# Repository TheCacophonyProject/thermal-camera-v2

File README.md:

# thermal-camera-v2

## Running tc2-panel.py (KiKit)

`tc2-panel.py` uses [KiKit](https://yaqwsx.github.io/KiKit/) to build the manufacturing panel from the individual board files.

```sh
# Create a venv that inherits the system site-packages (needed for pcbnew)
python3 -m venv --system-site-packages ~/.venvs/kikit
source ~/.venvs/kikit/bin/activate

# Install kikit and the other packages tc2-panel.py needs.
# pcbnewTransition is pinned >=0.5 because older versions assume a pre-KiCad-6
# pcbnew API (e.g. DRAWSEGMENT) and crash against current KiCad.
pip install kikit shapely "pcbnewTransition>=0.5"
```

Once the venv exists, running the panel script again only needs:

```sh
source ~/.venvs/kikit/bin/activate
cd /path/to/thermal-camera-v2
python3 tc2-panel.py
```

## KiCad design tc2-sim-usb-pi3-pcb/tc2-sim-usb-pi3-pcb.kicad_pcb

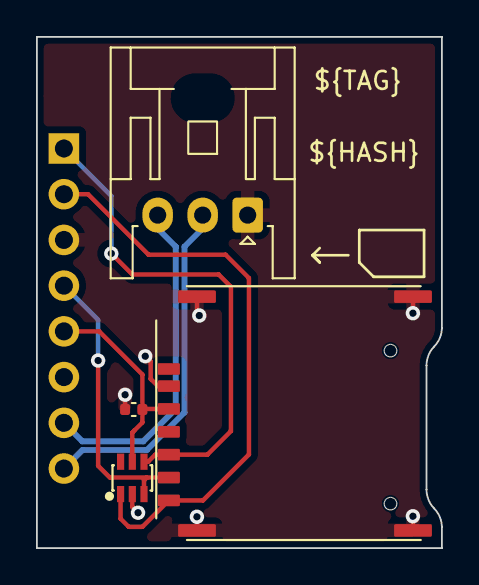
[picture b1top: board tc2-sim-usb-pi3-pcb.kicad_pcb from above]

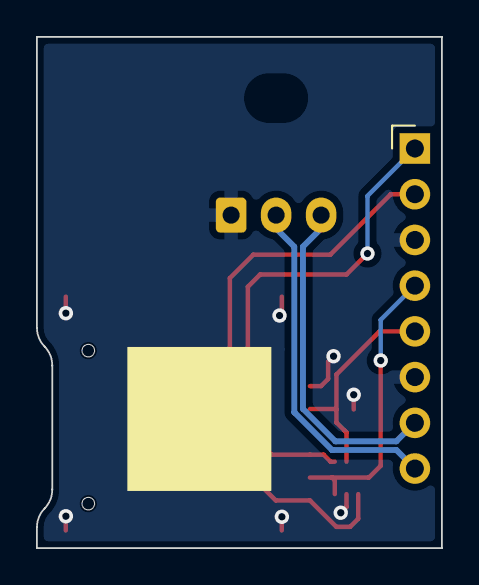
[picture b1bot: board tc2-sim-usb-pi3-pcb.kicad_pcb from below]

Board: 4 copper layers, 22.5 x 28.4 mm, 6 parts (2 on the bottom side), 7 nets.

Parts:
C1: 220nF; C_0402_1005Metric
D1: SMF05CT1G; SOT-363_L2.0-W1.3-P0.65-LS2.1-BR
J1: Conn_01x08; rpi3-usb-sim-PinHeader_1x08
J2: Conn_01x03; JST_XA_S03B-XASK-1_1x03_P2.50mm_Horizontal
U1: K-DYX-010
U2: JLCPCB_QR_8mm

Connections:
4G_USB_D+: J1.7, J2.3
4G_USB_D-: J1.8, J2.2
GND: C1.1, D1.2, J1.3, J1.6, J2.1, U1.C5 (Gnd), U1.MP, U1.MP_2 (MP), U1.MP_3 (MP), U1.MP_4 (MP)
USIM_CLK: D1.1, J1.2, U1.C3 (CLK)
USIM_DATA: D1.3, J1.4, U1.C7 (I/O)
USIM_RST: D1.4, J1.1, U1.C2 (RST)
USIM_VDD: C1.2, D1.5, J1.5, U1.C1 (Vcc)

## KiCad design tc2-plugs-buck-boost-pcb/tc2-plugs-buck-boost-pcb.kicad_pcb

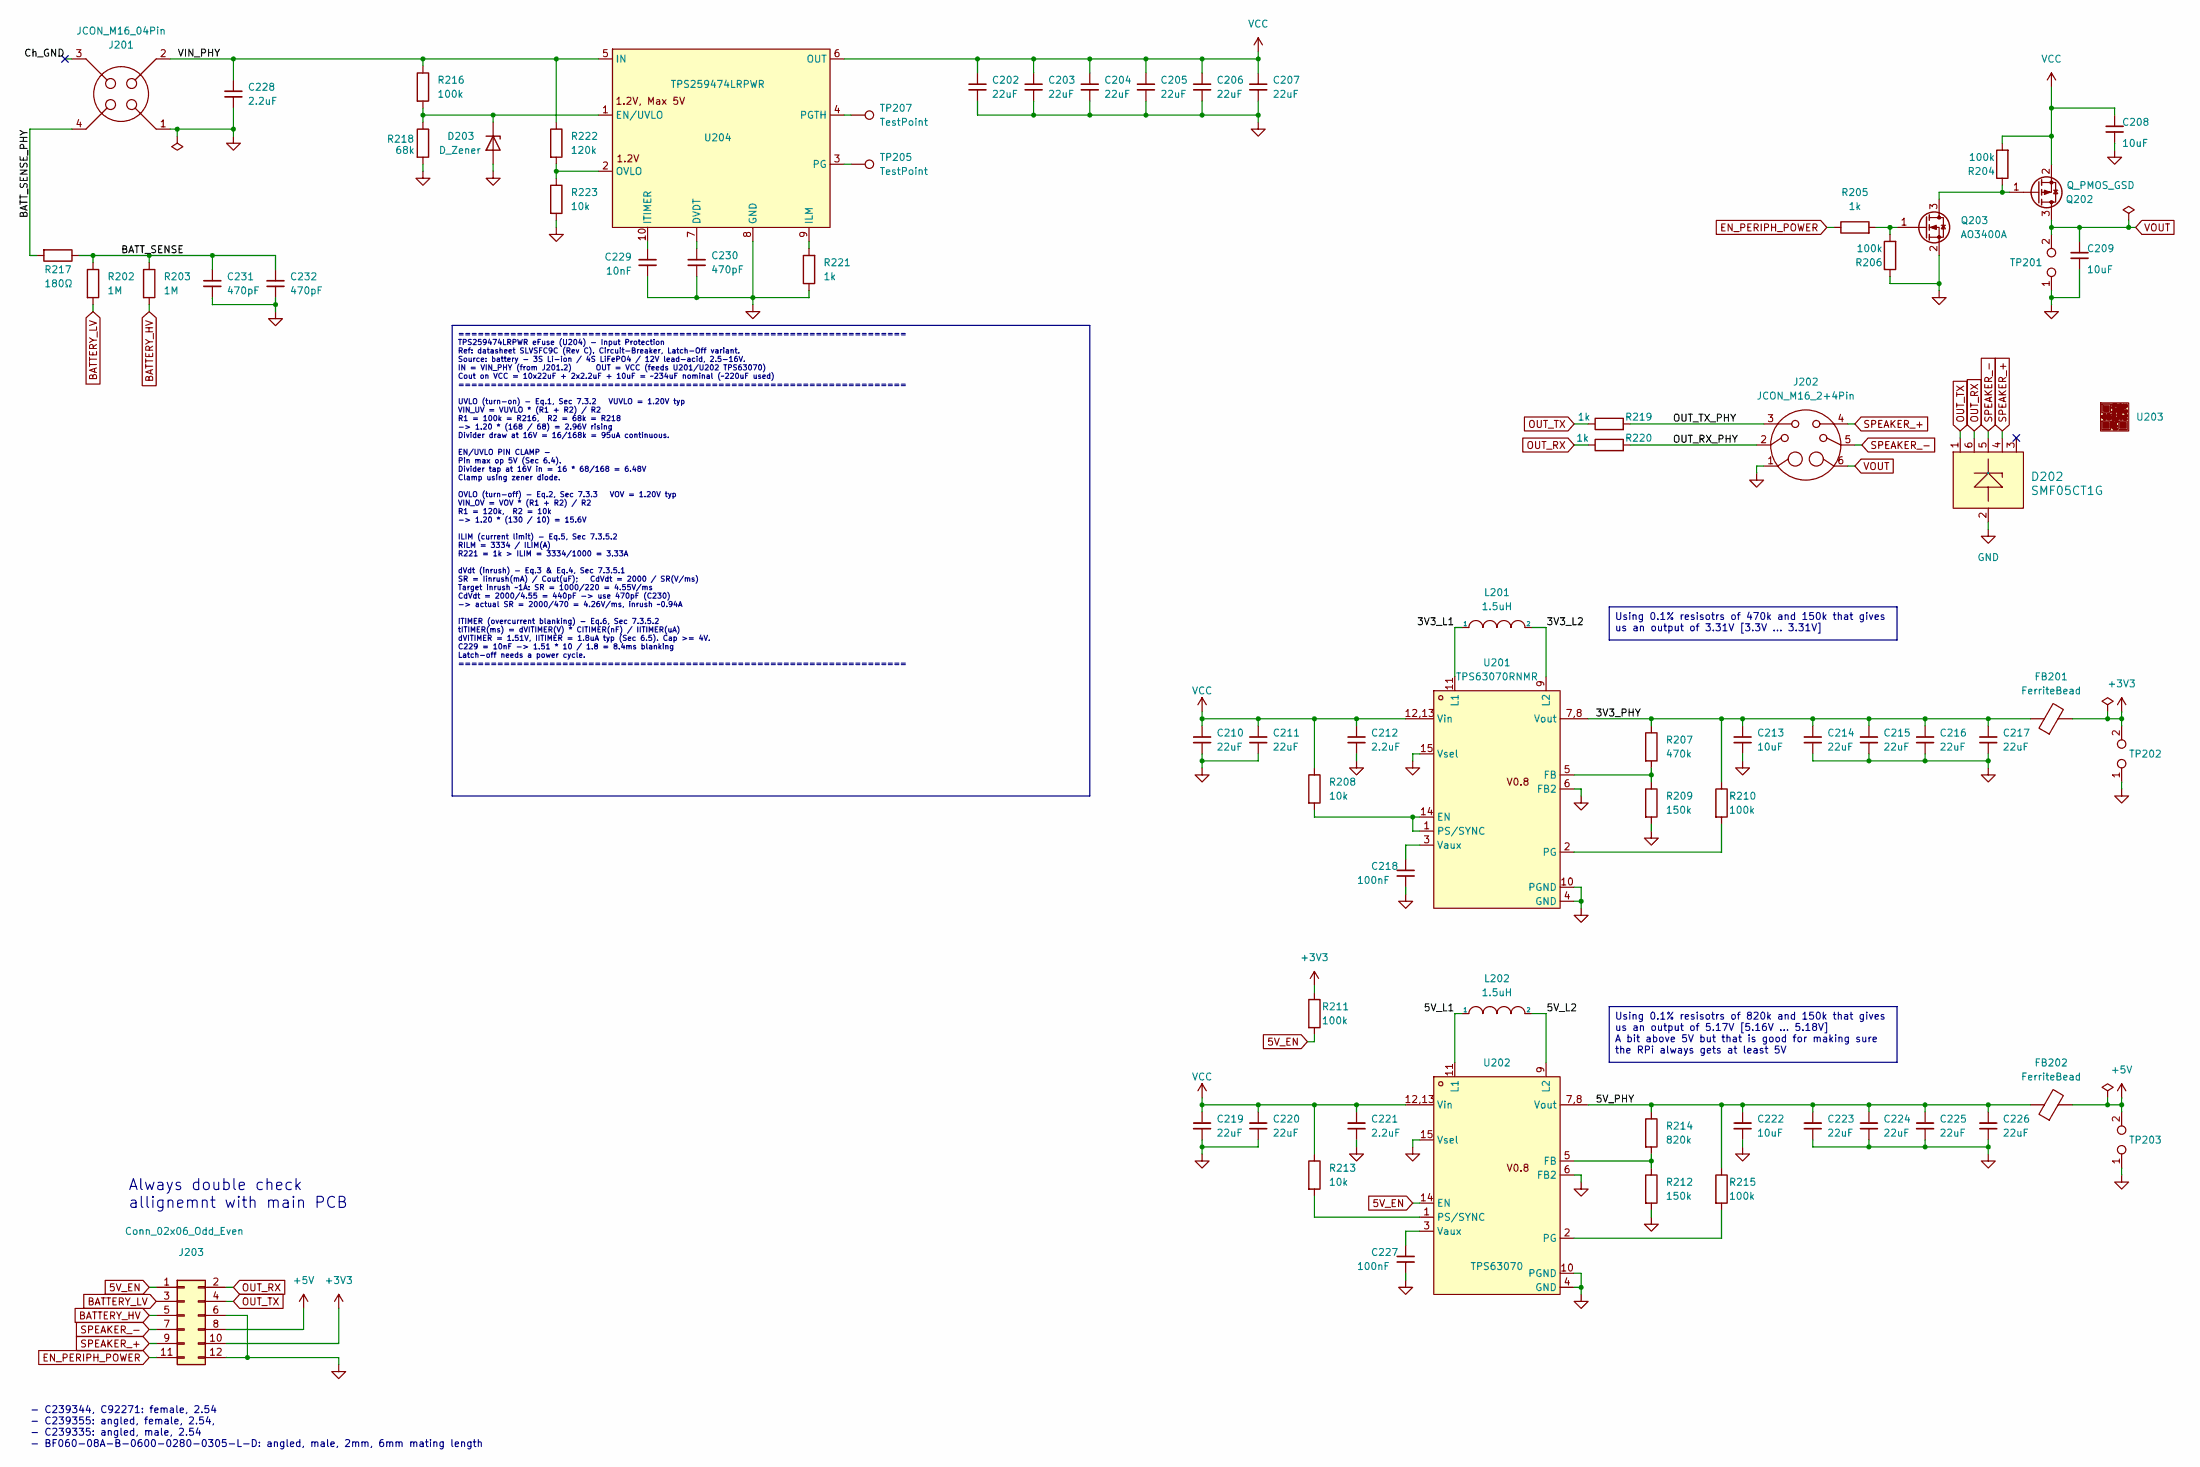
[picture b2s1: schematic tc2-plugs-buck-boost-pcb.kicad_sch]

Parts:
C202, C203, C204, C205, C206, C207, C210, C211, C219, C220: 22uF; C_0805_2012Metric; LCSC Part C45783
C208, C209: 10uF; C_0603_1608Metric; LCSC Part C19702
C212, C221, C228: 2.2uF; C_0402_1005Metric; LCSC Part C159814
C213, C222: 10uF; C_0402_1005Metric; LCSC Part C15525
C214, C215, C216, C217, C223, C224, C225, C226: 22uF; C_0603_1608Metric; LCSC Part C86295
C218, C227: 100nF; C_0402_1005Metric; LCSC Part C100072
C229: 10nF; C_0402_1005Metric; LCSC Part C15195
C230, C231, C232: 470pF; C_0402_1005Metric; LCSC Part C1537
D202: SMF05CT1G; SOT-363_L2.0-W1.3-P0.65-LS2.1-BR; LCSC Part C15879
D203: D_Zener; D_SOD-323; LCSC Part C136181
FB201, FB202: FerriteBead; L_0805_2012Metric; LCSC Part C76818
J201: JCON_M16_04Pin; jcon-4pin_m16
J202: JCON_M16_2+4Pin; jcon-2+4pin-m16
J203: Conn_02x06_Odd_Even; PinHeader_2x06_P2.00mm_Horizontal; Digikey 2073-BF060-12A-B-0600-0280-0305-L-D-ND
L201, L202: 1.5uH; L_1008_2520Metric; LCSC Part C5179452
Q202: Q_PMOS_GSD; SOT-23; LCSC Part C15127
Q203: AO3400A; SOT-23; LCSC Part C20917
R202, R203: 1M; R_0603_1608Metric; LCSC Part C326730
R204, R206, R210, R211, R215, R216: 100k; R_0402_1005Metric; LCSC Part C25741
R205, R219, R220, R221: 1k; R_0402_1005Metric; LCSC Part C11702
R207: 470k; R_0402_1005Metric; LCSC Part C319591
R208, R213, R223: 10k; R_0402_1005Metric; LCSC Part C25744
R209, R212: 150k; R_0402_1005Metric; LCSC Part C723770
R214: 820k; R_0402_1005Metric; LCSC Part C4042952
R217: 180Ω; R_0402_1005Metric; LCSC Part C38941
R218: 68k; R_0402_1005Metric; LCSC Part C445618
R222: 120k; R_0402_1005Metric; LCSC Part C25750
TP201, TP202, TP203: TestPoint_2Pole; test-point-2p
TP205, TP207: TestPoint; TP_PAD
U201: TPS63070RNMR; TPS63070; LCSC Part C109322
U202: TPS63070; LCSC Part C109322
U203: JLCPCB_QR_8mm
U204: TPS259474LRPWR; VQFN-10_L2.0-W2.0-P0.45-TL; LCSC Part C2864845

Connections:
5V_EN: J203.1, R211.2, U202.14 (EN)
+3V3: FB201.2, J203.10, R211.1, TP202.2
+5V: FB202.2, J203.8, TP203.2
/3V3_L1: L201.1, U201.11 (L1)
/3V3_L2: L201.2, U201.9 (L2)
/3V3_PHY: C213.1, C214.1, C215.1, C216.1, C217.1, FB201.1, R207.1, R210.1, U201.7,8 (Vout)
/5V_L1: L202.1, U202.11 (L1)
/5V_L2: L202.2, U202.9 (L2)
/5V_PHY: C222.1, C223.1, C224.1, C225.1, C226.1, FB202.1, R214.1, R215.1, U202.7,8 (Vout)
/BATT_SENSE: C231.1, C232.1, R202.1, R203.1, R217.1
/BATT_SENSE_PHY: J201.4, R217.2
/Ch_GND: J201.3
/OUT_RX_PHY: J202.2, R220.2
/OUT_TX_PHY: J202.3, R219.2
/VIN_PHY: C228.1, J201.2, R216.1, R222.1, U204.5 (IN)
BATTERY_HV: J203.5, R203.2
BATTERY_LV: J203.3, R202.2
EN_PERIPH_POWER: J203.11, R205.1
GND: C202.2, C203.2, C204.2, C205.2, C206.2, C207.2, C208.2, C209.2, C210.2, C211.2, C212.2, C213.2, C214.2, C215.2, C216.2, C217.2, C218.2, C219.2, C220.2, C221.2, C222.2, C223.2, C224.2, C225.2, C226.2, C227.2, C228.2, C229.2, C230.2, C231.2, C232.2, D202.2, D203.2 (A), J201.1, J202.1, J203.6, J203.12, Q203.2 (S), R206.1, R209.2, R212.2, R218.2, R221.1, R223.2, TP201.1, TP202.1, TP203.1, U201.4 (GND), U201.6 (FB2), U201.10 (PGND), U201.15 (Vsel), U202.4 (GND), U202.6 (FB2), U202.10 (PGND), U202.15 (Vsel), U204.8 (GND)
unnamed: D203.1 (K), R216.2, R218.1, U204.1 (EN/UVLO)
unnamed: Q202.1 (G), Q203.3 (D), R204.1
unnamed: Q203.1 (G), R205.2, R206.2
unnamed: R208.2, U201.1 (PS/SYNC), U201.14 (EN)
unnamed: R207.2, R209.1, U201.5 (FB)
unnamed: R210.2, U201.2 (PG)
unnamed: C218.1, U201.3 (Vaux)
unnamed: R212.1, R214.2, U202.5 (FB)
unnamed: R215.2, U202.2 (PG)
unnamed: R213.2, U202.1 (PS/SYNC)
unnamed: C227.1, U202.3 (Vaux)
unnamed: C230.1, U204.7 (DVDT)
unnamed: R221.2, U204.9 (ILM)
unnamed: C229.1, U204.10 (ITIMER)
unnamed: R222.2, R223.1, U204.2 (OVLO)
unnamed: TP205.1 (1_1), U204.3 (PG)
unnamed: TP207.1 (1_1), U204.4 (PGTH)
OUT_RX: D202.6, J203.2, R220.1
OUT_TX: D202.1, J203.4, R219.1
SPEAKER_+: D202.4, J202.4, J203.9
SPEAKER_-: D202.5, J202.5, J203.7
VCC: C202.1, C203.1, C204.1, C205.1, C206.1, C207.1, C208.1, C210.1, C211.1, C212.1, C219.1, C220.1, C221.1, Q202.2 (S), R204.2, R208.1, R213.1, U201.12,13 (Vin), U202.12,13 (Vin), U204.6 (OUT)
VOUT: C209.1, J202.6, Q202.3 (D), TP201.2

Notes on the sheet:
Always double check allignemnt with main PCB
- C239344, C92271: female, 2.54 - C239355: angled, female, 2.54, - C239335: angled, male, 2.54 - BF060-08A-B-0600-0280-0305-L-D: angled, male, 2mm, 6mm mating length
===================================================================== TPS259474LRPWR eFuse (U204) - Input Protection Ref: datasheet SLVSFC9C (Rev C). Circuit-Breaker, Latch-Off variant. Source: battery - 3S Li-ion / 4S LiFePO4 / 12V lead-acid, 2.5-16V. IN = VIN_PHY (from J201.2) OUT = VCC (feeds U2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
Using 0.1% resisotrs of 470k and 150k that gives us an output of 3.31V [3.3V ... 3.31V]
Using 0.1% resisotrs of 820k and 150k that gives us an output of 5.17V [5.16V ... 5.18V] A bit above 5V but that is good for making sure the RPi always gets at least 5V

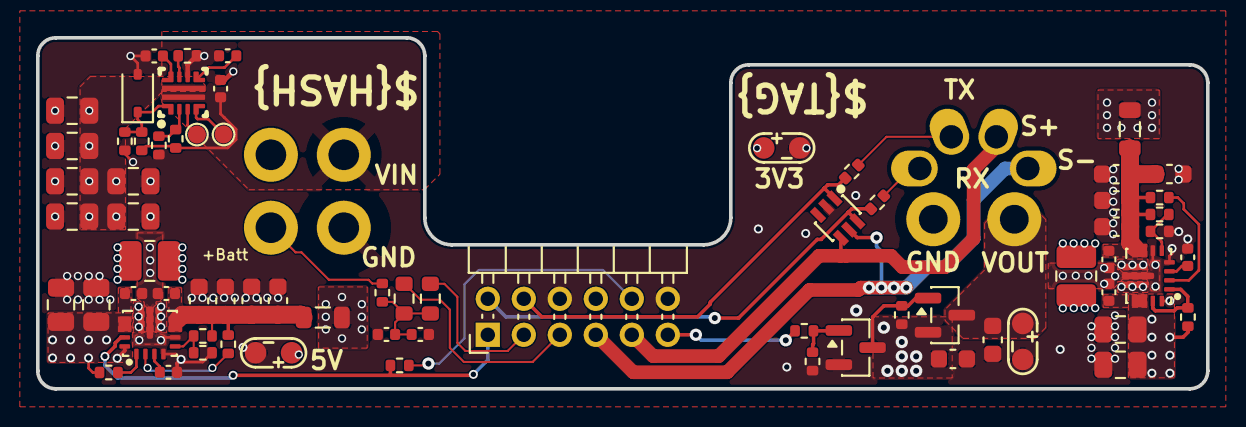
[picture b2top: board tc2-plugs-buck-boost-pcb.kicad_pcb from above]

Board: 6 copper layers, 65.0 x 19.5 mm, 73 parts (1 on the bottom side), 41 nets.

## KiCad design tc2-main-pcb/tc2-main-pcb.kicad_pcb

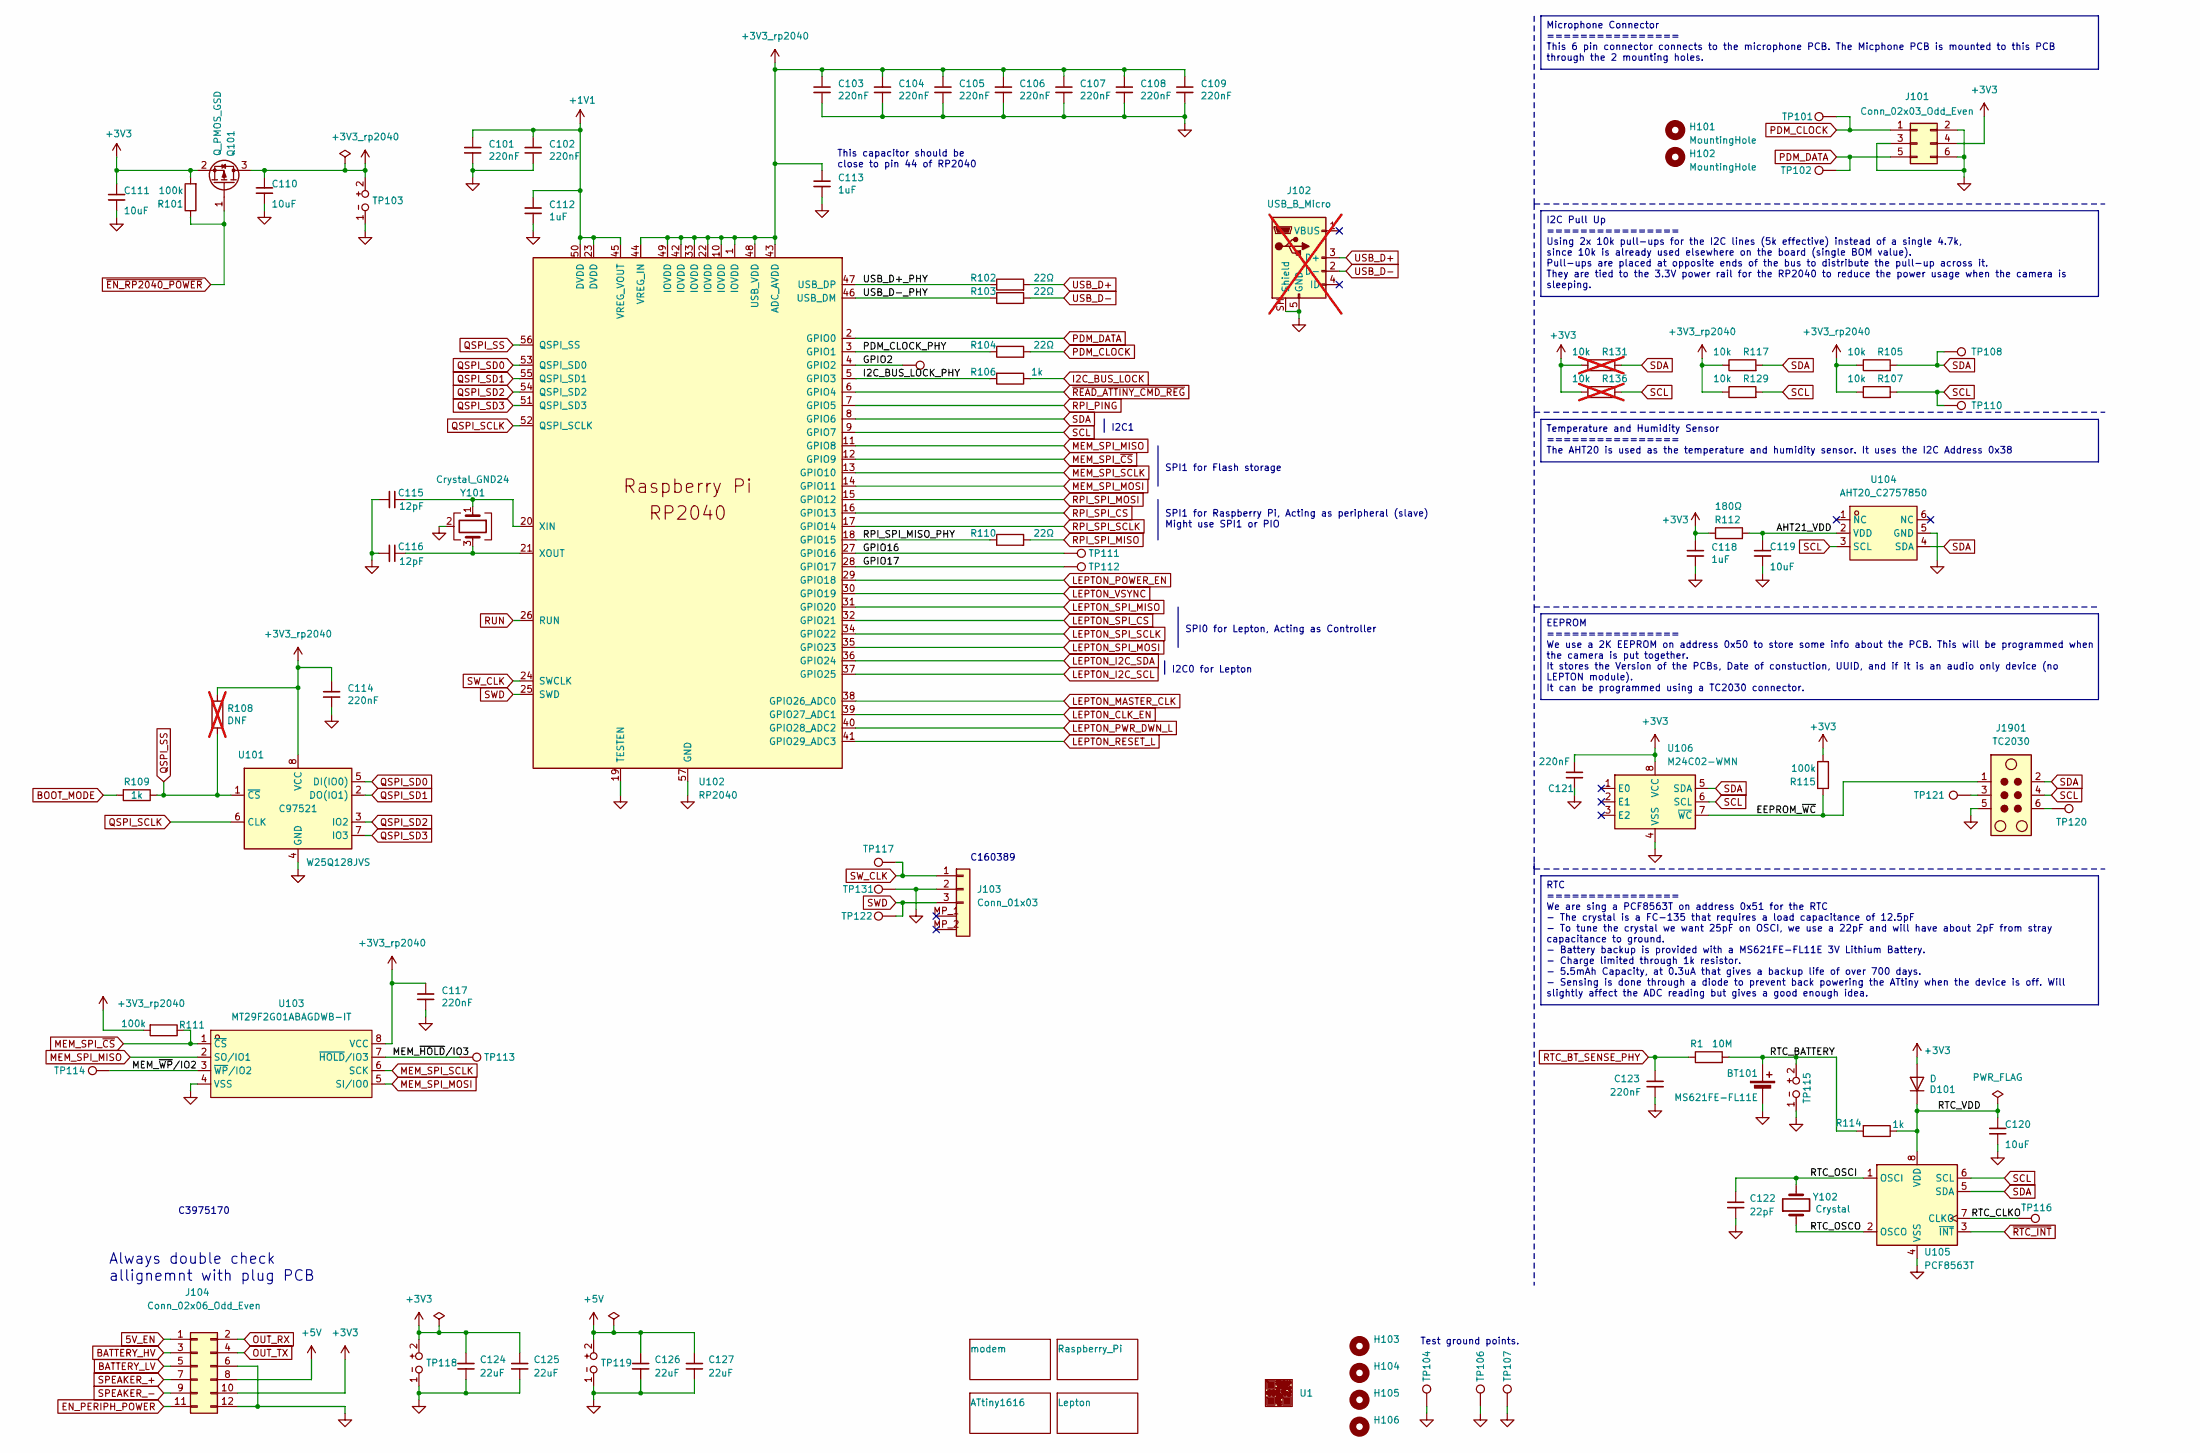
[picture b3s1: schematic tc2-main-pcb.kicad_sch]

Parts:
BT101: MS621FE-FL11E; CAP-SMD_FL11E; LCSC Part C80909
C101, C102, C103, C104, C105, C106, C107, C108, C109, C114, C117, C121, C123: 220nF; C_0402_1005Metric; LCSC Part C16772
C110, C111, C119, C120: 10uF; C_0603_1608Metric; LCSC Part C19702
C112, C113, C118: 1uF; C_0402_1005Metric; LCSC Part C52923
C115, C116: 12pF; C_0402_1005Metric; LCSC Part C1547
C122: 22pF; C_0402_1005Metric; LCSC Part C1555
C124, C125, C126, C127: 22uF; C_0603_1608Metric; LCSC Part C86295
D101: D; D_SOD-523; LCSC Part C668989
H101, H102: MountingHole; MountingHole_2.2mm_M2
H103, H104, H105, H106: MountingHole; MountingHole_3.2mm_M3
J101: Conn_02x03_Odd_Even; mic-pcb; LCSC Part C3975129
J102: USB_B_Micro; MICRO-USB-TH_MICRO-USB-A14; LCSC Part C145795; not fitted
J103: Conn_01x03; JST_SH_BM03B-SRSS-TB_1x03-1MP_P1.00mm_Vertical; LCSC Part C160389
J104: Conn_02x06_Odd_Even; power-pcb-3.1; Digikey BF100-12-A-D-1-0640-L-C
J1901: TC2030; Tag-Connect_TC2030-IDC-NL_2x03_P1.27mm_Vertical
Q101: Q_PMOS_GSD; SOT-23; LCSC Part C15127
R1: 10M; R_0402_1005Metric; LCSC Part C274900
R101, R111, R115: 100k; R_0402_1005Metric; LCSC Part C25741
R102, R103, R104, R110: 22Ω; R_0402_1005Metric; LCSC Part C25092
R105, R107, R117, R129: 10k; R_0402_1005Metric; LCSC Part C25744
R106, R109, R114: 1k; R_0402_1005Metric; LCSC Part C11702
R108: DNF; R_0402_1005Metric; not fitted
R112: 180Ω; R_0402_1005Metric; LCSC Part C38941
R131, R136: 10k; R_0402_1005Metric; LCSC Part C25744; not fitted
TP101, TP102, TP108, TP110, TP117, TP120, TP121, TP122, TP131: TestPoint; TestPoint_Pad_D1.0mm
TP103, TP115, TP118, TP119: TP_2P; test-point-2p
TP104, TP106, TP107: TestPoint; TestPoint_Loop_D2.54mm_Drill1.5mm_Beaded
TP109, TP111, TP112, TP113, TP114, TP116: TestPoint; TP
U1: JLCPCB_QR_8mm
U101: W25Q128JVS; SOIC-8_5.3x5.3mm_P1.27mm; LCSC Part C97521
U102: RP2040; RP2040-QFN-56; LCSC Part C2040
U103: MT29F2G01ABAGDWB-IT; U-PDFN-8_L6.0-W8.0-P1.27-BL; JLC Part Extended Part
U104: AHT20_C2757850; SENSOR-SMD_L3.0-W3.0-P1.00-BR; LCSC Part C2757850
U105: PCF8563T; SOIC-8_3.9x4.9mm_P1.27mm; LCSC Part C7440
U106: M24C02-WMN; SOIC-8_3.9x4.9mm_P1.27mm; LCSC Part C7562
Y101: Crystal_GND24; Crystal_SMD_3225-4Pin_3.2x2.5mm; LCSC Part C9002
Y102: Crystal; Crystal_SMD_3215-2Pin_3.2x1.5mm; LCSC Part C32346

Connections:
5V_EN: J104.1; also elsewhere on the board
+1V1: C101.1, C102.1, C112.1, U102.23 (DVDD), U102.45 (VREG_VOUT), U102.50 (DVDD)
+3V3: C111.1, C118.1, C121.2, C124.1, C125.1, D101.2 (A), J101.4, J104.10, Q101.2 (S), R101.2, R112.1, R115.2, R131.1, R136.1, TP118.2, U106.8 (VCC); also elsewhere on the board
+3V3_rp2040: C103.1, C104.1, C105.1, C106.1, C107.1, C108.1, C109.1, C110.1, C113.1, C114.1, C117.1, Q101.3 (D), R105.1, R107.1, R108.1, R111.2, R117.1, R129.1, TP103.2, U101.8 (VCC), U102.1 (IOVDD), U102.10 (IOVDD), U102.22 (IOVDD), U102.33 (IOVDD), U102.42 (IOVDD), U102.43 (ADC_AVDD), U102.44 (VREG_IN), U102.48 (USB_VDD), U102.49 (IOVDD), U103.8 (VCC)
+5V: C126.1, C127.1, J104.8, TP119.2; also elsewhere on the board
/AHT21_VDD: C119.1, R112.2, U104.2 (VDD)
/EEPROM_~WC: J1901.1, R115.1, U106.7 (~WC)
/GPIO2: TP109.1 (1_1), U102.4 (GPIO2)
/GPIO16: TP111.1 (1_1), U102.27 (GPIO16)
/GPIO17: TP112.1 (1_1), U102.28 (GPIO17)
/I2C_BUS_LOCK_PHY: R106.2, U102.5 (GPIO3)
/MEM_~HOLD/IO3: TP113.1 (1_1), U103.7 (~HOLD/IO3)
/MEM_~WP/IO2: TP114.1 (1_1), U103.3 (~WP/IO2)
/PDM_CLOCK_PHY: R104.1, U102.3 (GPIO1)
/RPI_SPI_MISO_PHY: R110.1, U102.18 (GPIO15)
/RTC_BATTERY: BT101.1 (+), R1.2, R114.2, TP115.2
/RTC_CLKO: TP116.1 (1_1), U105.7 (CLKO)
/RTC_OSCI: C122.1, U105.1 (OSCI), Y102.2
/RTC_OSCO: U105.2 (OSCO), Y102.1
/RTC_VDD: C120.1, D101.1 (K), R114.1, U105.8 (VDD)
/USB_D+_PHY: R102.1, U102.47 (USB_DP)
/USB_D-_PHY: R103.1, U102.46 (USB_DM)
BATTERY_HV: J104.3; also elsewhere on the board
BATTERY_LV: J104.5; also elsewhere on the board
BOOT_MODE: R109.2; also elsewhere on the board
EN_PERIPH_POWER: J104.11; also elsewhere on the board
GND: BT101.2 (-), C101.2, C102.2, C103.2, C104.2, C105.2, C106.2, C107.2, C108.2, C109.2, C110.2, C111.2, C112.2, C113.2, C114.2, C115.1, C116.1, C117.2, C118.2, C119.2, C120.2, C121.1, C122.2, C123.2, C124.2, C125.2, C126.2, C127.2, J101.2, J101.3, J101.6, J102.5 (GND), J102.SH (Shield), J103.2, J104.6, J104.12, J1901.5, TP103.1, TP104.1 (1_1), TP106.1 (1_1), TP107.1 (1_1), TP115.1, TP118.1, TP119.1, TP131.1 (1_1), U101.4 (GND), U102.19 (TESTEN), U102.57 (GND), U103.4 (VSS), U104.5 (GND), U105.4 (VSS), U106.4 (VSS), Y101.2 (G), Y101.4 (G); also elsewhere on the board
I2C_BUS_LOCK: R106.1; also elsewhere on the board
LEPTON_CLK_EN: U102.39 (GPIO27_ADC1); also elsewhere on the board
LEPTON_I2C_SCL: U102.37 (GPIO25); also elsewhere on the board
LEPTON_I2C_SDA: U102.36 (GPIO24); also elsewhere on the board
LEPTON_MASTER_CLK: U102.38 (GPIO26_ADC0); also elsewhere on the board
LEPTON_POWER_EN: U102.29 (GPIO18); also elsewhere on the board
LEPTON_PWR_DWN_L: U102.40 (GPIO28_ADC2); also elsewhere on the board
LEPTON_RESET_L: U102.41 (GPIO29_ADC3); also elsewhere on the board
LEPTON_SPI_CS: U102.32 (GPIO21); also elsewhere on the board
LEPTON_SPI_MISO: U102.31 (GPIO20); also elsewhere on the board
LEPTON_SPI_MOSI: U102.35 (GPIO23); also elsewhere on the board
LEPTON_SPI_SCLK: U102.34 (GPIO22); also elsewhere on the board
LEPTON_VSYNC: U102.30 (GPIO19); also elsewhere on the board
MEM_SPI_MISO: U102.11 (GPIO8), U103.2 (SO/IO1)
MEM_SPI_MOSI: U102.14 (GPIO11), U103.5 (SI/IO0)
MEM_SPI_SCLK: U102.13 (GPIO10), U103.6 (SCK)
MEM_SPI_~CS: R111.1, U102.12 (GPIO9), U103.1 (~CS)
unnamed: J1901.3, TP121.1 (1_1)
unnamed: J1901.6, TP120.1 (1_1)
unnamed: C115.2, U102.20 (XIN), Y101.1
unnamed: C116.2, U102.21 (XOUT), Y101.3
OUT_RX: J104.2; also elsewhere on the board
OUT_TX: J104.4; also elsewhere on the board
PDM_CLOCK: J101.1, R104.2, TP101.1 (1_1)
PDM_DATA: J101.5, TP102.1 (1_1), U102.2 (GPIO0)
QSPI_SCLK: U101.6 (CLK), U102.52 (QSPI_SCLK)
QSPI_SD0: U101.5 (DI(IO0)), U102.53 (QSPI_SD0)
QSPI_SD1: U101.2 (DO(IO1)), U102.55 (QSPI_SD1)
QSPI_SD2: U101.3 (IO2), U102.54 (QSPI_SD2)
QSPI_SD3: U101.7 (IO3), U102.51 (QSPI_SD3)
QSPI_SS: R108.2, R109.1, U101.1 (~CS), U102.56 (QSPI_SS)
RPI_PING: U102.7 (GPIO5); also elsewhere on the board
RPI_SPI_CS: U102.16 (GPIO13); also elsewhere on the board
RPI_SPI_MISO: R110.2; also elsewhere on the board
RPI_SPI_MOSI: U102.15 (GPIO12); also elsewhere on the board
RPI_SPI_SCLK: U102.17 (GPIO14); also elsewhere on the board
RTC_BT_SENSE_PHY: C123.1, R1.1; also elsewhere on the board
RUN: U102.26 (RUN); also elsewhere on the board
SCL: J1901.4, R107.2, R129.2, R136.2, TP110.1 (1_1), U102.9 (GPIO7), U104.3 (SCL), U105.6 (SCL), U106.6 (SCL); also elsewhere on the board
SDA: J1901.2, R105.2, R117.2, R131.2, TP108.1 (1_1), U102.8 (GPIO6), U104.4 (SDA), U105.5 (SDA), U106.5 (SDA); also elsewhere on the board
SPEAKER_+: J104.7; also elsewhere on the board
SPEAKER_-: J104.9; also elsewhere on the board
SWD: J103.3, TP122.1 (1_1), U102.25 (SWD); also elsewhere on the board
SW_CLK: J103.1, TP117.1 (1_1), U102.24 (SWCLK); also elsewhere on the board
USB_D+: J102.3 (D+), R102.2
USB_D-: J102.2 (D-), R103.2
~EN_RP2040_POWER: Q101.1 (G), R101.1; also elsewhere on the board
~READ_ATTINY_CMD_REG: U102.6 (GPIO4); also elsewhere on the board
~RTC_INT: U105.3 (~INT); also elsewhere on the board

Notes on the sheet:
C160389
Test ground points.
SPI0 for Lepton, Acting as Controller
I2C1
C3975170
Always double check allignemnt with plug PCB
I2C0 for Lepton
This capacitor should be close to pin 44 of RP2040
SPI1 for Raspberry Pi, Acting as peripheral (slave) Might use SPI1 or PIO
SPI1 for Flash storage
I2C Pull Up ================ Using 2x 10k pull-ups for the I2C lines (5k effective) instead of a single 4.7k, since 10k is already used elsewhere on the board (single BOM value). Pull-ups are placed at opposite ends of the bus to distribute the pull-up across it. They are tied to the 3.3V power rai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
RTC ================ We are sing a PCF8563T on address 0x51 for the RTC - The crystal is a FC-135 that requires a load capacitance of 12.5pF - To tune the crystal we want 25pF on OSCI, we use a 22pF and will have about 2pF from stray capacitance to ground. - Battery backup is provided with a MS621F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
Temperature and Humidity Sensor ================ The AHT20 is used as the temperature and humidity sensor. It uses the I2C Address 0x38
Microphone Connector ================ This 6 pin connector connects to the microphone PCB. The Micphone PCB is mounted to this PCB through the 2 mounting holes.
EEPROM ================ We use a 2K EEPROM on address 0x50 to store some info about the PCB. This will be programmed when the camera is put together. It stores the Version of the PCBs, Date of constuction, UUID, and if it is an audio only device (no LEPTON module). It can be programmed using a TC20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

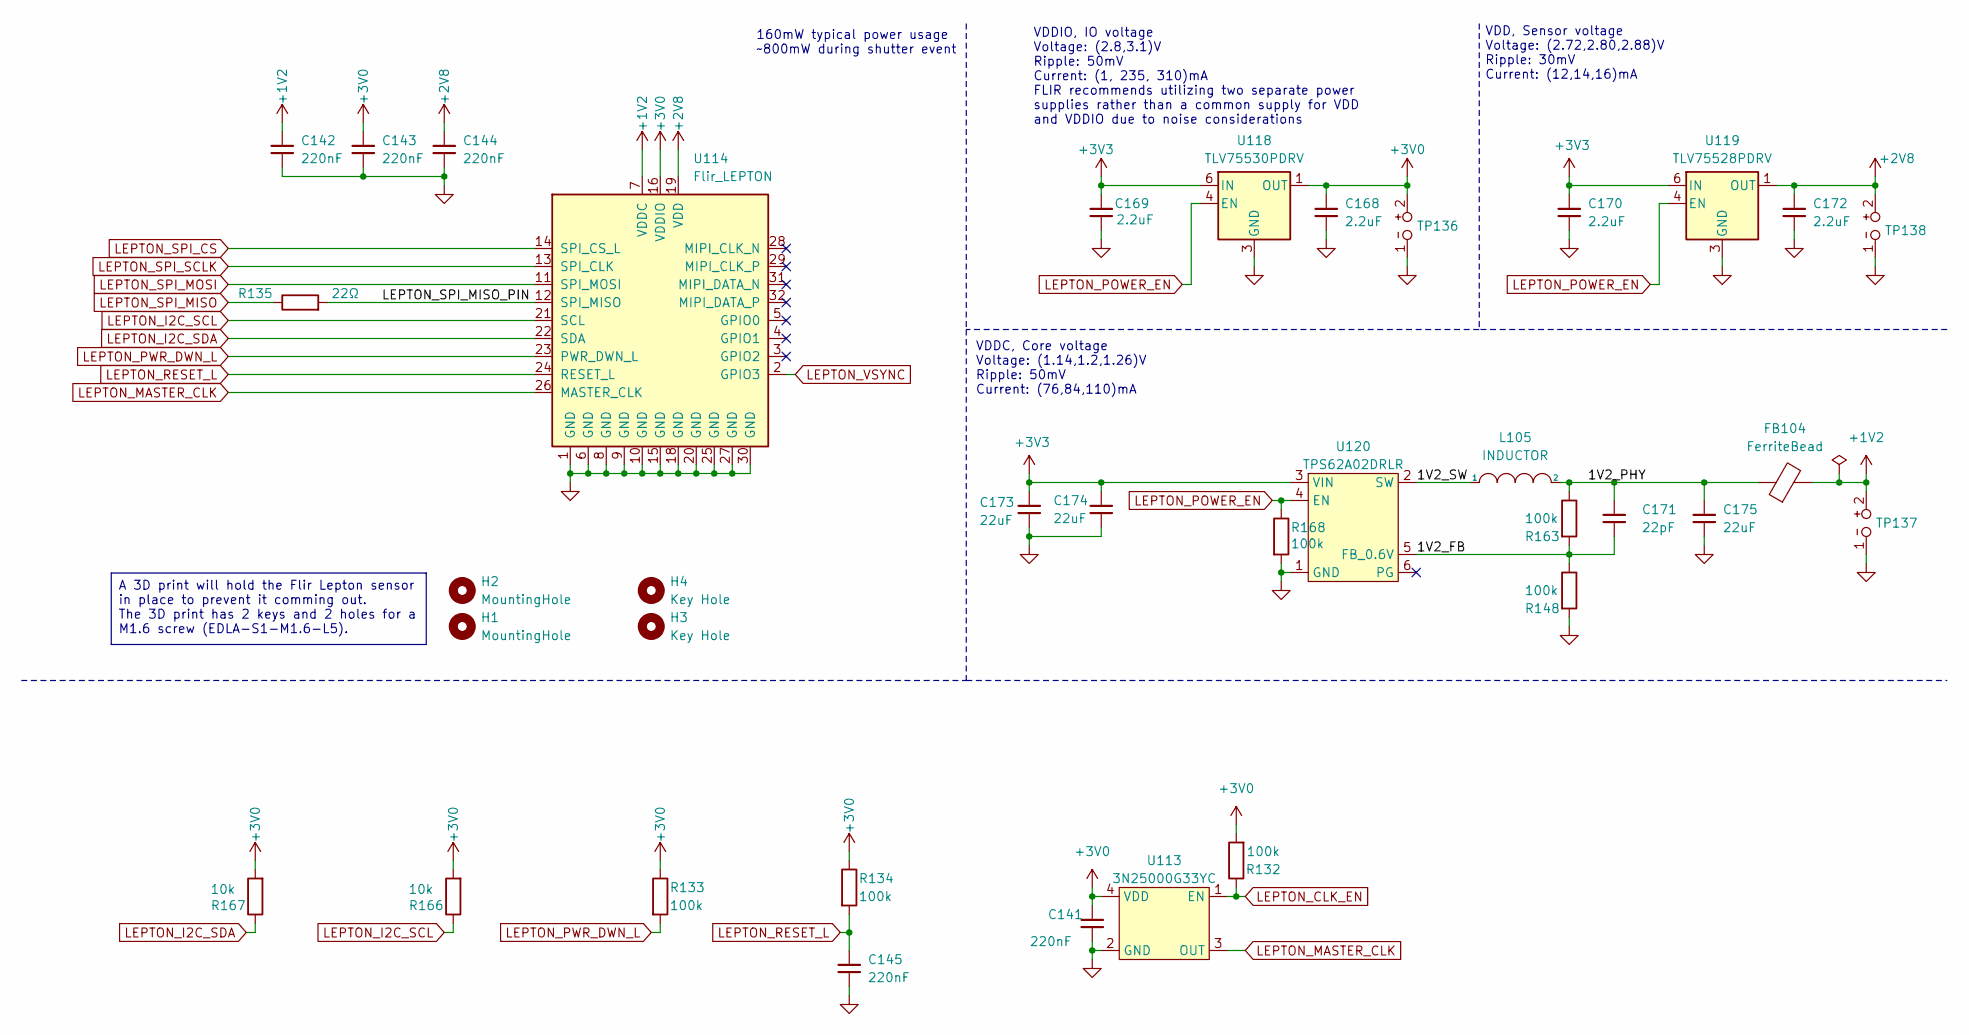
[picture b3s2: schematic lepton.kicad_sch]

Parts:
C141, C142, C143, C144, C145: 220nF; C_0402_1005Metric; LCSC Part C16772
C168, C169, C170, C172: 2.2uF; C_0402_1005Metric; LCSC Part C12530
C171: 22pF; C_0402_1005Metric; LCSC Part C1555
C173, C174, C175: 22uF; C_0603_1608Metric; LCSC Part C86295
FB104: FerriteBead; L_0805_2012Metric; LCSC Part C76818
H1, H2: MountingHole; MountingHole_1.8mm_M1.6
H3, H4: Key Hole; KeyHole_1.8mm
L105: INDUCTOR; L_1008_2520Metric; LCSC Part C285917
R132: 100k; R_0402_1005Metric; MPN RC1005F103CS; LCSC Part C25741
R133, R134, R148, R163, R168: 100k; R_0402_1005Metric; LCSC Part C25741
R135: 22Ω; R_0402_1005Metric; LCSC Part C25092
R166, R167: 10k; R_0402_1005Metric; LCSC Part C25744
TP136, TP137, TP138: TP_2P; test-point-2p
U113: 3N25000G33YC; Oscillator_SMD_Abracon_ASE-4Pin_3.2x2.5mm; JLCPCB C252341
U114: Flir_LEPTON; MOLEX_105028-1001; MPN 1050281001; LCSC Part C585422
U118: TLV75530PDRV; WSON-6-1EP_2x2mm_P0.65mm_EP1x1.6mm; LCSC Part C2859948
U119: TLV75528PDRV; WSON-6-1EP_2x2mm_P0.65mm_EP1x1.6mm; LCSC Part C2865214
U120: TPS62A02DRLR; SOT-563; LCSC Part C5350187

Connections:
+1V2: C142.1, FB104.2, TP137.2, U114.7 (VDDC)
+2V8: C144.1, C172.1, TP138.2, U114.19 (VDD), U119.1 (OUT)
+3V0: C141.1, C143.1, C168.1, R132.2, R133.1, R134.1, R166.2, R167.2, TP136.2, U113.4 (VDD), U114.16 (VDDIO), U118.1 (OUT)
+3V3: C169.1, C170.1, C173.1, C174.1, U118.6 (IN), U119.6 (IN), U120.3 (VIN); also elsewhere on the board
/Lepton/1V2_FB: C171.2, R148.1, R163.2, U120.5 (FB_0.6V)
/Lepton/1V2_PHY: C171.1, C175.1, FB104.1, L105.2, R163.1
/Lepton/1V2_SW: L105.1, U120.2 (SW)
/Lepton/LEPTON_SPI_MISO_PIN: R135.2, U114.12 (SPI_MISO)
GND: C141.2, C142.2, C143.2, C144.2, C145.2, C168.2, C169.2, C170.2, C172.2, C173.2, C174.2, C175.2, R148.2, R168.2, TP136.1, TP137.1, TP138.1, U113.2 (GND), U114.1 (GND), U114.6 (GND), U114.8 (GND), U114.9 (GND), U114.10 (GND), U114.15 (GND), U114.18 (GND), U114.20 (GND), U114.25 (GND), U114.27 (GND), U114.30 (GND), U118.3 (GND), U118.7 (GND), U119.3 (GND), U119.7 (GND), U120.1 (GND); also elsewhere on the board
LEPTON_CLK_EN: R132.1, U113.1 (EN); also elsewhere on the board
LEPTON_I2C_SCL: R166.1, U114.21 (SCL); also elsewhere on the board
LEPTON_I2C_SDA: R167.1, U114.22 (SDA); also elsewhere on the board
LEPTON_MASTER_CLK: U113.3 (OUT), U114.26 (MASTER_CLK); also elsewhere on the board
LEPTON_POWER_EN: R168.1, U118.4 (EN), U119.4 (EN), U120.4 (EN); also elsewhere on the board
LEPTON_PWR_DWN_L: R133.2, U114.23 (PWR_DWN_L); also elsewhere on the board
LEPTON_RESET_L: C145.1, R134.2, U114.24 (RESET_L); also elsewhere on the board
LEPTON_SPI_CS: U114.14 (SPI_CS_L); also elsewhere on the board
LEPTON_SPI_MISO: R135.1; also elsewhere on the board
LEPTON_SPI_MOSI: U114.11 (SPI_MOSI); also elsewhere on the board
LEPTON_SPI_SCLK: U114.13 (SPI_CLK); also elsewhere on the board
LEPTON_VSYNC: U114.2 (GPIO3); also elsewhere on the board

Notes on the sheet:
VDDIO, IO voltage Voltage: (2.8,3.1)V Ripple: 50mV Current: (1, 235, 310)mA FLIR recommends utilizing two separate power supplies rather than a common supply for VDD and VDDIO due to noise considerations
VDDC, Core voltage Voltage: (1.14,1.2,1.26)V Ripple: 50mV Current: (76,84,110)mA
VDD, Sensor voltage Voltage: (2.72,2.80,2.88)V Ripple: 30mV Current: (12,14,16)mA
160mW typical power usage ~800mW during shutter event
A 3D print will hold the Flir Lepton sensor in place to prevent it comming out. The 3D print has 2 keys and 2 holes for a M1.6 screw (EDLA-S1-M1.6-L5).
